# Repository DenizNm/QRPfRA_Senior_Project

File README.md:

# QRPfRA: Quadruped Robot Platform for Research Applications

## About the Project
This project develops a low-cost, modular quadruped robot to enhance accessibility to robotics education and research. Leveraging the open-source SpotMicro design, the robot is engineered with three degrees of freedom per leg, using readily available servo motors and a Raspberry Pi 4B for computation. It incorporates a 9-DoF IMU and a Raspberry Pi camera for environmental sensing and navigation. The control and processing software, built in Python, utilizes TensorFlow/TFLite and OpenCV for tasks such as motion planning and image processing.

## Features
- **Cost-Effective Design:** Utilizes off-the-shelf components to maintain affordability.
- **Modular and Scalable:** Easy to modify and extend, perfect for educational purposes.
- **Interdisciplinary Approach:** Combines mechanical, electrical, and computer engineering.

## Table of Contents
- [Contact](#contact)
- [Acknowledgements](#acknowledgements)

## Contact
Deniz Namlısesli - [deniz.namlisesli@std.yeditepe.edu.tr](mailto:deniz.namlisesli@std.yeditepe.edu.tr)

Project Link: [https://github.com/DenizNm/QRPfRA_Senior_Project](https://github.com/DenizNm/QRPfRA_Senior_Project)

## Acknowledgements
- [SpotMicro Community](https://spotmicroai.readthedocs.io)
- [TensorFlow](https://tensorflow.org)
- [OpenCV](https://opencv.org)
- All other libraries and frameworks used in this project are acknowledged in the project documentation.

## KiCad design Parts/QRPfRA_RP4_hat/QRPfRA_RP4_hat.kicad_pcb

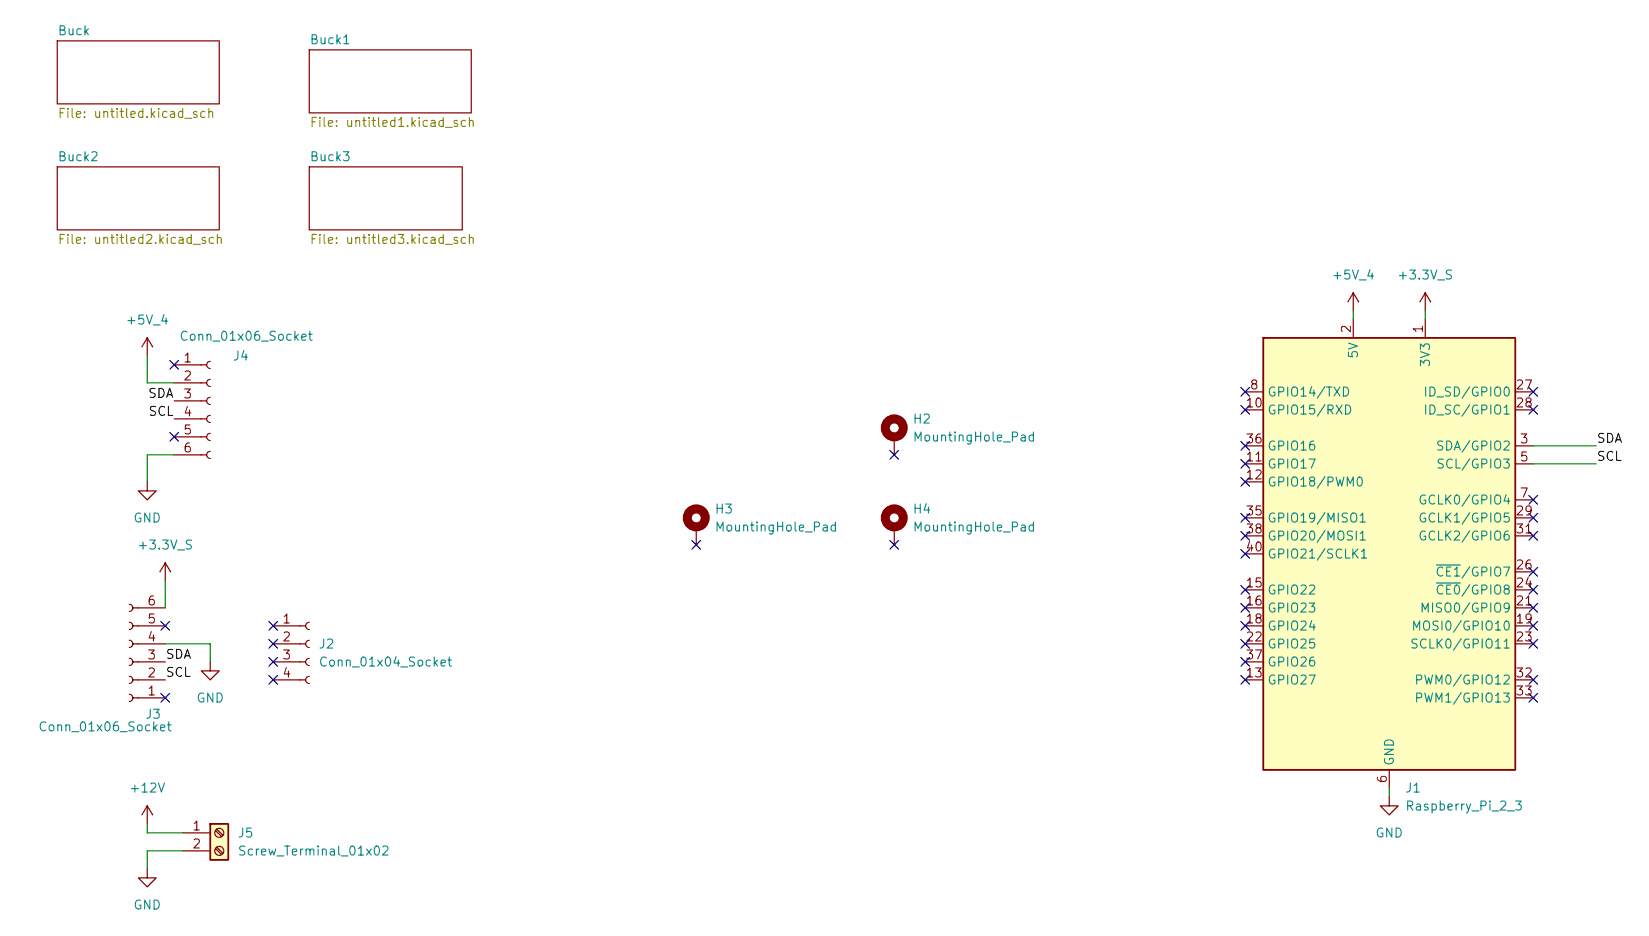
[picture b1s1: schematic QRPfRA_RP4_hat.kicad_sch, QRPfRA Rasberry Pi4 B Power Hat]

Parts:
H2, H3, H4: MountingHole_Pad; MountingHole_2.7mm_Pad
J1: Raspberry_Pi_2_3; PinHeader_2x20_P2.54mm_Vertical
J2: Conn_01x04_Socket; PinHeader_1x04_P2.54mm_Vertical
J3, J4: Conn_01x06_Socket; PinHeader_1x06_P2.54mm_Vertical
J5: Screw_Terminal_01x02; TerminalBlock_4Ucon_1x02_P3.50mm_Vertical

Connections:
+3.3V_S: J1.1 (3V3), J1.17 (3V3), J3.6
+5V_4: J1.2 (5V), J1.4 (5V), J4.2; also elsewhere on the board
+12V: J5.1; also elsewhere on the board
/SCL: J1.5 (SCL/GPIO3), J3.2, J4.4
/SDA: J1.3 (SDA/GPIO2), J3.3, J4.3
GND: J1.6 (GND), J1.9 (GND), J1.14 (GND), J1.20 (GND), J1.25 (GND), J1.30 (GND), J1.34 (GND), J1.39 (GND), J3.4, J4.6, J5.2; also elsewhere on the board

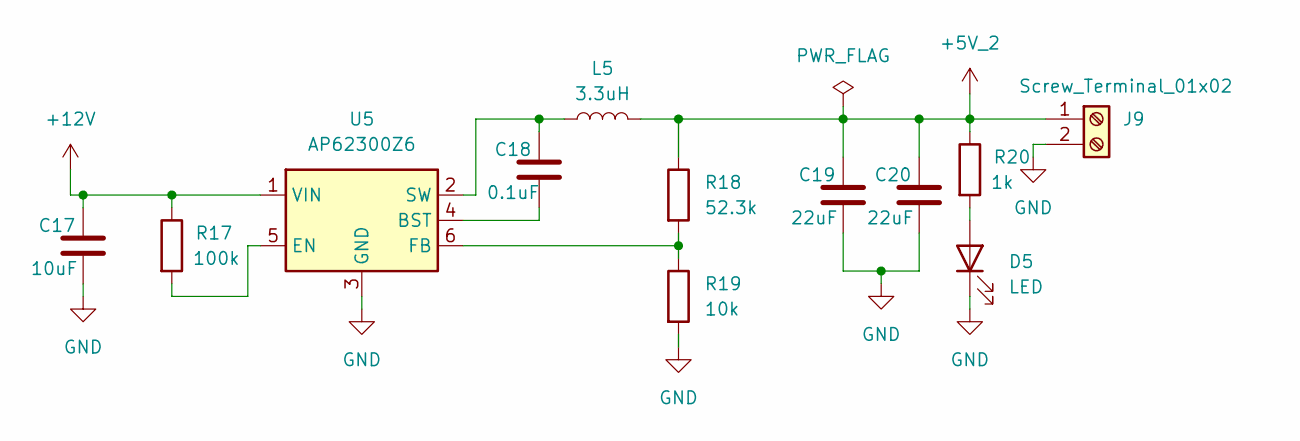
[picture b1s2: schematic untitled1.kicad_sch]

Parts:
C17: 10uF; C_1206_3216Metric
C18: 0.1uF; C_0603_1608Metric
C19, C20: 22uF; C_1206_3216Metric
D5: LED; LED_0603_1608Metric
J9: Screw_Terminal_01x02; TerminalBlock_4Ucon_1x02_P3.50mm_Vertical
L5: 3.3uH; L_TDK_VLS6045EX_VLS6045AF
R17: 100k; R_0603_1608Metric
R18: 52.3k; R_0603_1608Metric
R19: 10k; R_0603_1608Metric
R20: 1k; R_0603_1608Metric
U5: AP62300Z6; SOT-563

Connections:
+5V_2: C19.1, C20.1, J9.1, L5.2, R18.1, R20.1
+12V: C17.1, R17.1, U5.1 (VIN); also elsewhere on the board
GND: C17.2, C19.2, C20.2, D5.1 (K), J9.2, R19.2, U5.3 (GND); also elsewhere on the board
unnamed: D5.2 (A), R20.2
unnamed: C18.2, U5.4 (BST)
unnamed: R17.2, U5.5 (EN)
unnamed: R18.2, R19.1, U5.6 (FB)
unnamed: C18.1, L5.1, U5.2 (SW)

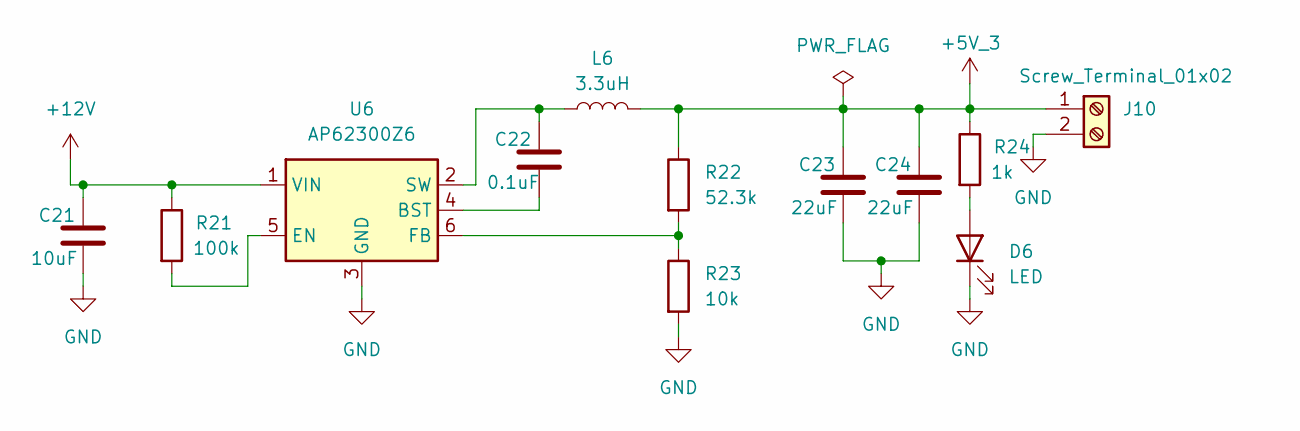
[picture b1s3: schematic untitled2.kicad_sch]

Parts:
C21: 10uF; C_1206_3216Metric
C22: 0.1uF; C_0603_1608Metric
C23, C24: 22uF; C_1206_3216Metric
D6: LED; LED_0603_1608Metric
J10: Screw_Terminal_01x02; TerminalBlock_4Ucon_1x02_P3.50mm_Vertical
L6: 3.3uH; L_TDK_VLS6045EX_VLS6045AF
R21: 100k; R_0603_1608Metric
R22: 52.3k; R_0603_1608Metric
R23: 10k; R_0603_1608Metric
R24: 1k; R_0603_1608Metric
U6: AP62300Z6; SOT-563

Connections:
+5V_3: C23.1, C24.1, J10.1, L6.2, R22.1, R24.1
+12V: C21.1, R21.1, U6.1 (VIN); also elsewhere on the board
GND: C21.2, C23.2, C24.2, D6.1 (K), J10.2, R23.2, U6.3 (GND); also elsewhere on the board
unnamed: D6.2 (A), R24.2
unnamed: C22.2, U6.4 (BST)
unnamed: R21.2, U6.5 (EN)
unnamed: R22.2, R23.1, U6.6 (FB)
unnamed: C22.1, L6.1, U6.2 (SW)

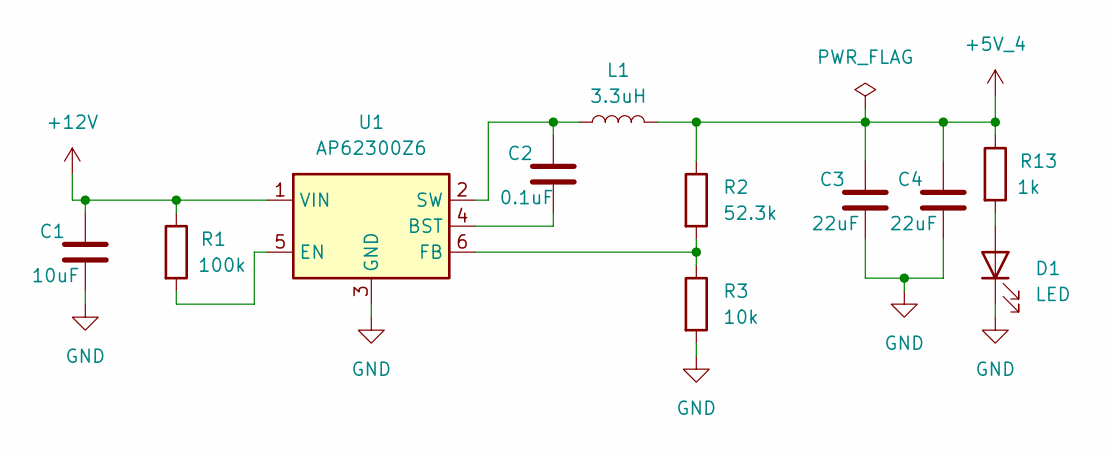
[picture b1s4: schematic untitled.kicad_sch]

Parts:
C1: 10uF; C_1206_3216Metric
C2: 0.1uF; C_0603_1608Metric
C3, C4: 22uF; C_1206_3216Metric
D1: LED; LED_0603_1608Metric
L1: 3.3uH; L_TDK_VLS6045EX_VLS6045AF
R1: 100k; R_0603_1608Metric
R2: 52.3k; R_0603_1608Metric
R3: 10k; R_0603_1608Metric
R13: 1k; R_0603_1608Metric
U1: AP62300Z6; SOT-563

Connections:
+5V_4: C3.1, C4.1, L1.2, R2.1, R13.1; also elsewhere on the board
+12V: C1.1, R1.1, U1.1 (VIN); also elsewhere on the board
GND: C1.2, C3.2, C4.2, D1.1 (K), R3.2, U1.3 (GND); also elsewhere on the board
unnamed: D1.2 (A), R13.2
unnamed: C2.2, U1.4 (BST)
unnamed: R1.2, U1.5 (EN)
unnamed: R2.2, R3.1, U1.6 (FB)
unnamed: C2.1, L1.1, U1.2 (SW)

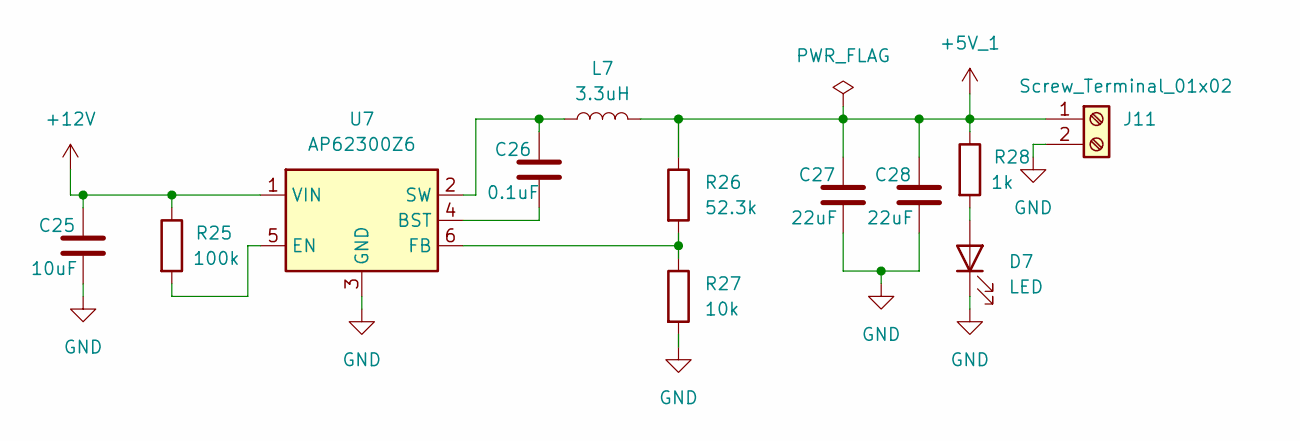
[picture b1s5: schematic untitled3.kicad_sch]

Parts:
C25: 10uF; C_1206_3216Metric
C26: 0.1uF; C_0603_1608Metric
C27, C28: 22uF; C_1206_3216Metric
D7: LED; LED_0603_1608Metric
J11: Screw_Terminal_01x02; TerminalBlock_4Ucon_1x02_P3.50mm_Vertical
L7: 3.3uH; L_TDK_VLS6045EX_VLS6045AF
R25: 100k; R_0603_1608Metric
R26: 52.3k; R_0603_1608Metric
R27: 10k; R_0603_1608Metric
R28: 1k; R_0603_1608Metric
U7: AP62300Z6; SOT-563

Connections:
+5V_1: C27.1, C28.1, J11.1, L7.2, R26.1, R28.1
+12V: C25.1, R25.1, U7.1 (VIN); also elsewhere on the board
GND: C25.2, C27.2, C28.2, D7.1 (K), J11.2, R27.2, U7.3 (GND); also elsewhere on the board
unnamed: D7.2 (A), R28.2
unnamed: C26.2, U7.4 (BST)
unnamed: R25.2, U7.5 (EN)
unnamed: R26.2, R27.1, U7.6 (FB)
unnamed: C26.1, L7.1, U7.2 (SW)

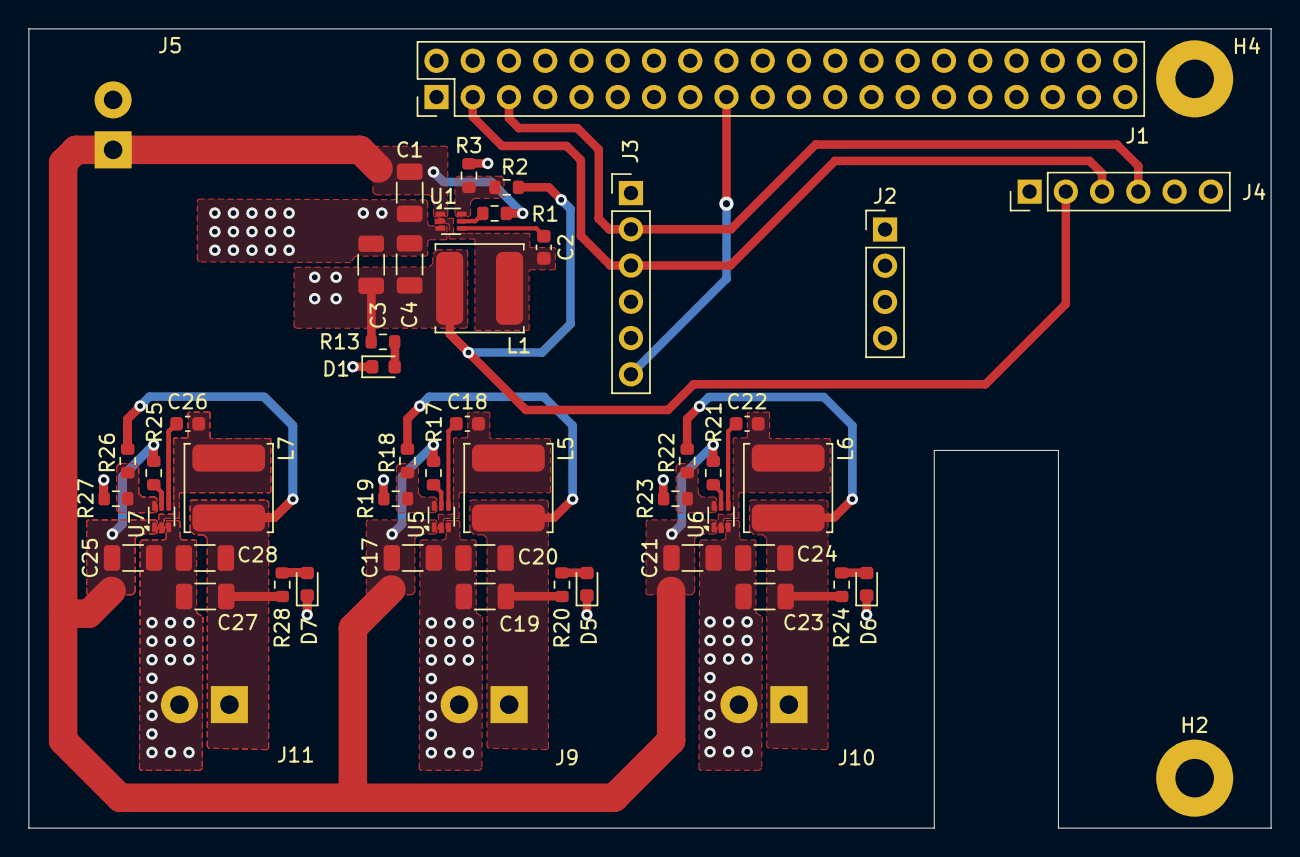
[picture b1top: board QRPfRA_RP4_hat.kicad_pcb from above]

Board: 2 copper layers, 87.0 x 56.0 mm, 54 parts (0 on the bottom side), 29 nets.

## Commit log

2024-01-23 Initial commit of MuJoCo definition for SpotMicro body
2024-01-25 Part costs, left leg IK model and scene definition
2024-01-26 Left leg IK model update, Right leg IK model added with necessary xml and notebook files
2024-01-26 Renaming
2024-01-30 Controllers
2024-01-31 Daily update
2024-01-31 Daily update v2
2024-02-01 Right IK model is working correctly, left leg IK model must be fixed
2024-02-04 Right legs hindlimb axis changed
2024-03-04 Open Loop Trot Walking Added with TROT_controller.py
2024-03-14 Trot walking with P controller
2024-03-31 Relative path recognition included.
2024-04-07 TROR classes added with usage.
2024-05-02 New TROT controller added, ultrasonic range sensors removed
2024-05-05 Extended body mes is added alongside modified scene and model definition files
2024-05-05 RPi4 Update
2024-05-05 General improvements
2024-05-06 Raspberry Pi 4 Power-Servo-IMU Hat KiCad Files
2024-05-12 Table Updated
2024-05-14 Updated cost list, changes to QRPfRA class, and modifications on TROT_controller.py
2024-05-16 Modification to XML models
